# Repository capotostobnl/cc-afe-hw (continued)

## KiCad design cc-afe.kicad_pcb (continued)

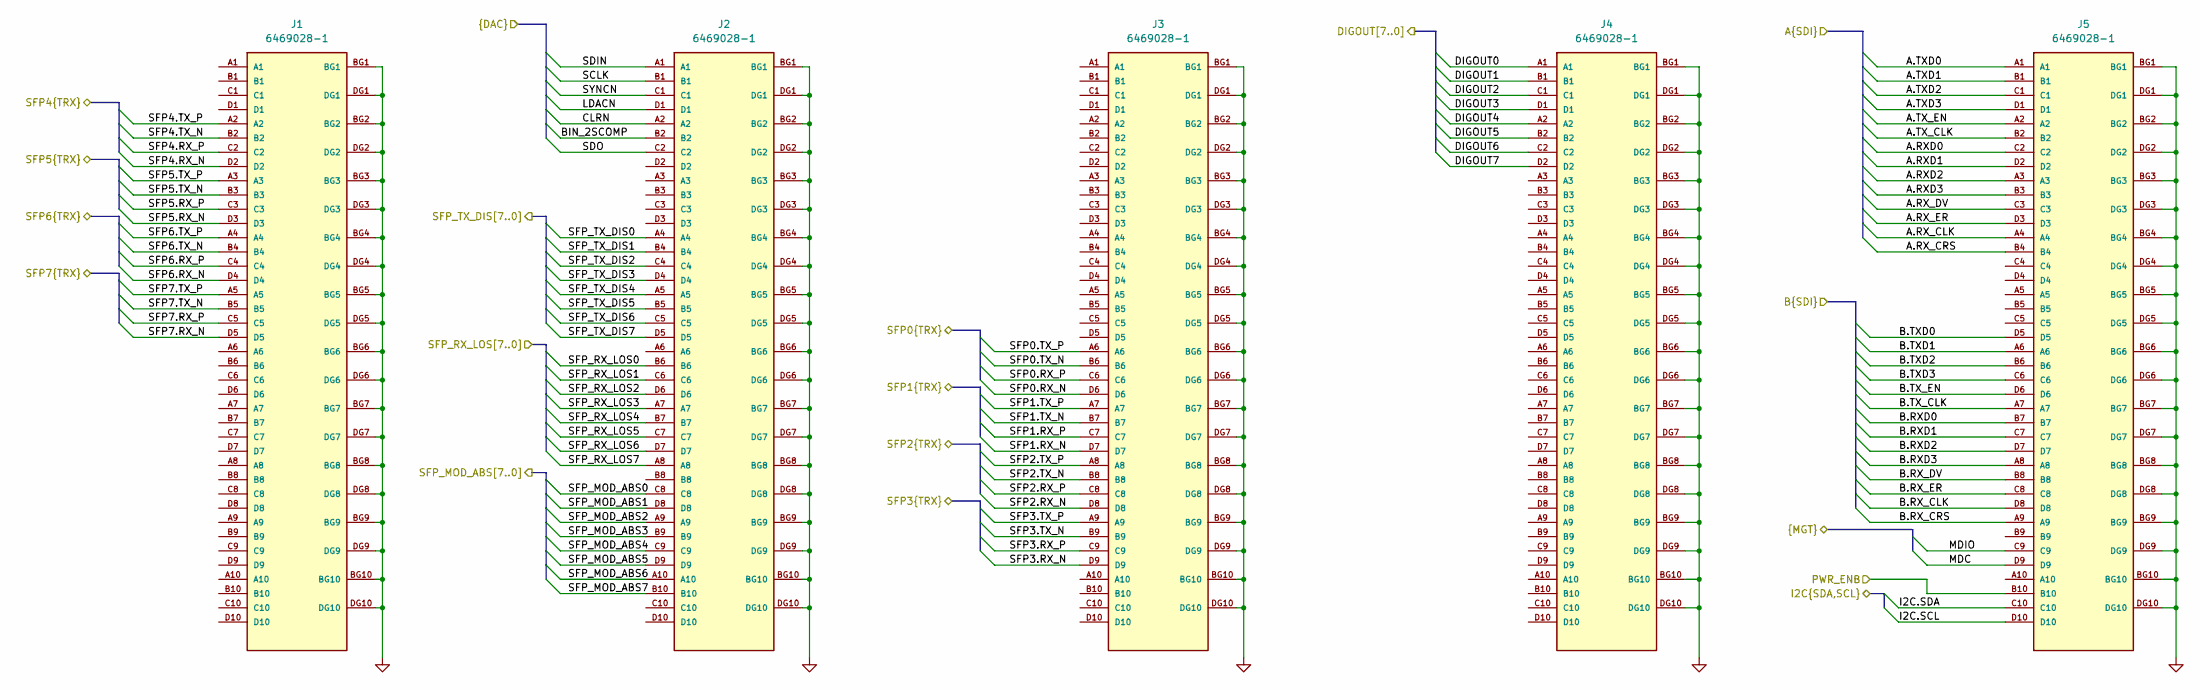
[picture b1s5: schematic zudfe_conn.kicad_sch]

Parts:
J1, J2, J3, J4, J5: 6469028-1; TE_6469028-1; PARTREV E

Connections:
/DAC/BIN_2SCOMP: J2.B2; also elsewhere on the board
/DAC/CLRN: J2.A2; also elsewhere on the board
/DAC/LDACN: J2.D1; also elsewhere on the board
/DAC/SCLK: J2.B1; also elsewhere on the board
/DAC/SDIN: J2.A1; also elsewhere on the board
/DAC/SDO: J2.C2
/DAC/SYNCN: J2.C1; also elsewhere on the board
/Digital Outputs/DIGOUT0: J4.A1; also elsewhere on the board
/Digital Outputs/DIGOUT1: J4.B1; also elsewhere on the board
/Digital Outputs/DIGOUT2: J4.C1; also elsewhere on the board
/Digital Outputs/DIGOUT3: J4.D1; also elsewhere on the board
/Digital Outputs/DIGOUT4: J4.A2; also elsewhere on the board
/Digital Outputs/DIGOUT5: J4.B2; also elsewhere on the board
/Digital Outputs/DIGOUT6: J4.C2; also elsewhere on the board
/Digital Outputs/DIGOUT7: J4.D2; also elsewhere on the board
/Regulators/PWR_ENB: J5.B10; also elsewhere on the board
/SDI/A.RXD0: J5.C2; also elsewhere on the board
/SDI/A.RXD1: J5.D2; also elsewhere on the board
/SDI/A.RXD2: J5.A3; also elsewhere on the board
/SDI/A.RXD3: J5.B3; also elsewhere on the board
/SDI/A.RX_CLK: J5.A4; also elsewhere on the board
/SDI/A.RX_CRS: J5.B4; also elsewhere on the board
/SDI/A.RX_DV: J5.C3; also elsewhere on the board
/SDI/A.RX_ER: J5.D3; also elsewhere on the board
/SDI/A.TXD0: J5.A1; also elsewhere on the board
/SDI/A.TXD1: J5.B1; also elsewhere on the board
/SDI/A.TXD2: J5.C1; also elsewhere on the board
/SDI/A.TXD3: J5.D1; also elsewhere on the board
/SDI/A.TX_CLK: J5.B2; also elsewhere on the board
/SDI/A.TX_EN: J5.A2; also elsewhere on the board
/SDI/B.RXD0: J5.B7; also elsewhere on the board
/SDI/B.RXD1: J5.C7; also elsewhere on the board
/SDI/B.RXD2: J5.D7; also elsewhere on the board
/SDI/B.RXD3: J5.A8; also elsewhere on the board
/SDI/B.RX_CLK: J5.D8; also elsewhere on the board
/SDI/B.RX_CRS: J5.A9; also elsewhere on the board
/SDI/B.RX_DV: J5.B8; also elsewhere on the board
/SDI/B.RX_ER: J5.C8; also elsewhere on the board
/SDI/B.TXD0: J5.D5; also elsewhere on the board
/SDI/B.TXD1: J5.A6; also elsewhere on the board
/SDI/B.TXD2: J5.B6; also elsewhere on the board
/SDI/B.TXD3: J5.C6; also elsewhere on the board
/SDI/B.TX_CLK: J5.A7; also elsewhere on the board
/SDI/B.TX_EN: J5.D6; also elsewhere on the board
/SDI/MDC: J5.D9; also elsewhere on the board
/SDI/MDIO: J5.C9; also elsewhere on the board
/SFP/I2C.SCL: J5.D10; also elsewhere on the board
/SFP/I2C.SDA: J5.C10; also elsewhere on the board
/SFP/SFP0.RX_N: J3.D6; also elsewhere on the board
/SFP/SFP0.RX_P: J3.C6; also elsewhere on the board
/SFP/SFP0.TX_N: J3.B6; also elsewhere on the board
/SFP/SFP0.TX_P: J3.A6; also elsewhere on the board
/SFP/SFP1.RX_N: J3.D7; also elsewhere on the board
/SFP/SFP1.RX_P: J3.C7; also elsewhere on the board
/SFP/SFP1.TX_N: J3.B7; also elsewhere on the board
/SFP/SFP1.TX_P: J3.A7; also elsewhere on the board
/SFP/SFP2.RX_N: J3.D8; also elsewhere on the board
/SFP/SFP2.RX_P: J3.C8; also elsewhere on the board
/SFP/SFP2.TX_N: J3.B8; also elsewhere on the board
/SFP/SFP2.TX_P: J3.A8; also elsewhere on the board
/SFP/SFP3.RX_N: J3.D9; also elsewhere on the board
/SFP/SFP3.RX_P: J3.C9; also elsewhere on the board
/SFP/SFP3.TX_N: J3.B9; also elsewhere on the board
/SFP/SFP3.TX_P: J3.A9; also elsewhere on the board
/SFP/SFP4.RX_N: J1.D2; also elsewhere on the board
/SFP/SFP4.RX_P: J1.C2; also elsewhere on the board
/SFP/SFP4.TX_N: J1.B2; also elsewhere on the board
/SFP/SFP4.TX_P: J1.A2; also elsewhere on the board
/SFP/SFP5.RX_N: J1.D3; also elsewhere on the board
/SFP/SFP5.RX_P: J1.C3; also elsewhere on the board
/SFP/SFP5.TX_N: J1.B3; also elsewhere on the board
/SFP/SFP5.TX_P: J1.A3; also elsewhere on the board
/SFP/SFP6.RX_N: J1.D4; also elsewhere on the board
/SFP/SFP6.RX_P: J1.C4; also elsewhere on the board
/SFP/SFP6.TX_N: J1.B4; also elsewhere on the board
/SFP/SFP6.TX_P: J1.A4; also elsewhere on the board
/SFP/SFP7.RX_N: J1.D5; also elsewhere on the board
/SFP/SFP7.RX_P: J1.C5; also elsewhere on the board
/SFP/SFP7.TX_N: J1.B5; also elsewhere on the board
/SFP/SFP7.TX_P: J1.A5; also elsewhere on the board
/SFP/SFP_MOD_ABS0: J2.C8; also elsewhere on the board
/SFP/SFP_MOD_ABS1: J2.D8; also elsewhere on the board
/SFP/SFP_MOD_ABS2: J2.A9; also elsewhere on the board
/SFP/SFP_MOD_ABS3: J2.B9; also elsewhere on the board
/SFP/SFP_MOD_ABS4: J2.C9; also elsewhere on the board
/SFP/SFP_MOD_ABS5: J2.D9; also elsewhere on the board
/SFP/SFP_MOD_ABS6: J2.A10; also elsewhere on the board
/SFP/SFP_MOD_ABS7: J2.B10; also elsewhere on the board
/SFP/SFP_RX_LOS0: J2.B6; also elsewhere on the board
/SFP/SFP_RX_LOS1: J2.C6; also elsewhere on the board
/SFP/SFP_RX_LOS2: J2.D6; also elsewhere on the board
/SFP/SFP_RX_LOS3: J2.A7; also elsewhere on the board
/SFP/SFP_RX_LOS4: J2.B7; also elsewhere on the board
/SFP/SFP_RX_LOS5: J2.C7; also elsewhere on the board
/SFP/SFP_RX_LOS6: J2.D7; also elsewhere on the board
/SFP/SFP_RX_LOS7: J2.A8; also elsewhere on the board
/SFP/SFP_TX_DIS0: J2.A4; also elsewhere on the board
/SFP/SFP_TX_DIS1: J2.B4; also elsewhere on the board
/SFP/SFP_TX_DIS2: J2.C4; also elsewhere on the board
/SFP/SFP_TX_DIS3: J2.D4; also elsewhere on the board
/SFP/SFP_TX_DIS4: J2.A5; also elsewhere on the board
/SFP/SFP_TX_DIS5: J2.B5; also elsewhere on the board
/SFP/SFP_TX_DIS6: J2.C5; also elsewhere on the board
/SFP/SFP_TX_DIS7: J2.D5; also elsewhere on the board
GND: J1.BG1, J1.BG2, J1.BG3, J1.BG4, J1.BG5, J1.BG6, J1.BG7, J1.BG8, J1.BG9, J1.BG10, J1.DG1, J1.DG2, J1.DG3, J1.DG4, J1.DG5, J1.DG6, J1.DG7, J1.DG8, J1.DG9, J1.DG10, J2.BG1, J2.BG2, J2.BG3, J2.BG4, J2.BG5, J2.BG6, J2.BG7, J2.BG8, J2.BG9, J2.BG10, J2.DG1, J2.DG2, J2.DG3, J2.DG4, J2.DG5, J2.DG6, J2.DG7, J2.DG8, J2.DG9, J2.DG10, J3.BG1, J3.BG2, J3.BG3, J3.BG4, J3.BG5, J3.BG6, J3.BG7, J3.BG8, J3.BG9, J3.BG10, J3.DG1, J3.DG2, J3.DG3, J3.DG4, J3.DG5, J3.DG6, J3.DG7, J3.DG8, J3.DG9, J3.DG10, J4.BG1, J4.BG2, J4.BG3, J4.BG4, J4.BG5, J4.BG6, J4.BG7, J4.BG8, J4.BG9, J4.BG10, J4.DG1, J4.DG2, J4.DG3, J4.DG4, J4.DG5, J4.DG6, J4.DG7, J4.DG8, J4.DG9, J4.DG10, J5.BG1, J5.BG2, J5.BG3, J5.BG4, J5.BG5, J5.BG6, J5.BG7, J5.BG8, J5.BG9, J5.BG10, J5.DG1, J5.DG2, J5.DG3, J5.DG4, J5.DG5, J5.DG6, J5.DG7, J5.DG8, J5.DG9, J5.DG10; also elsewhere on the board

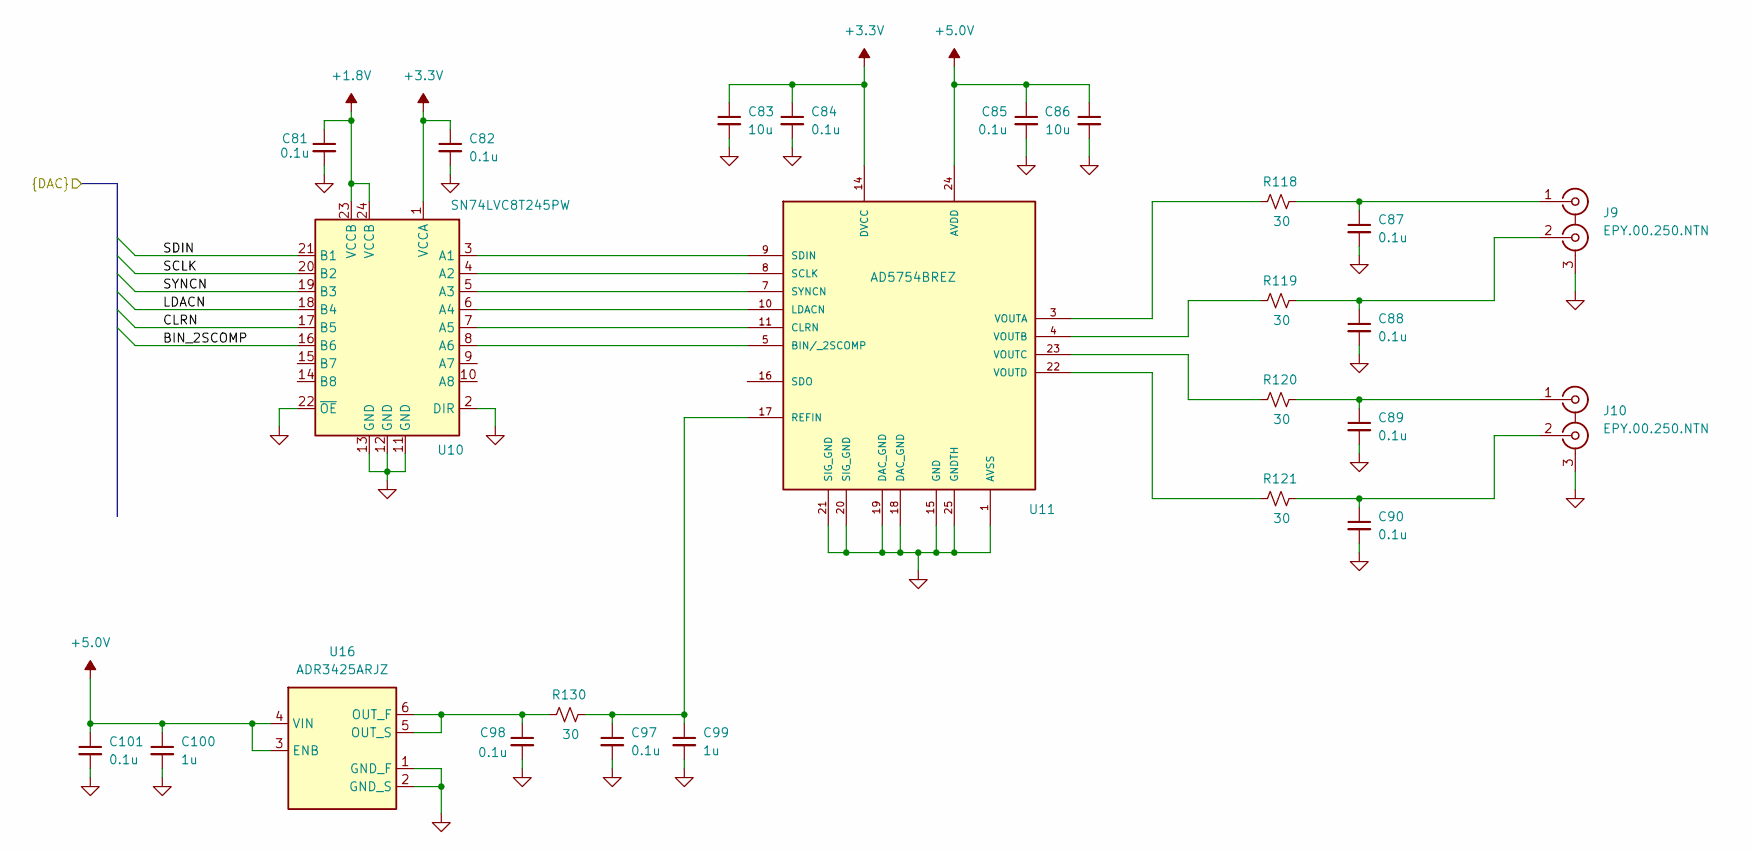
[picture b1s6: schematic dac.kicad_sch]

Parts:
C81, C82, C84, C85, C87, C88, C89, C90, C97, C98, C101: 0.1u; C_0603_1608Metric; Voltage 50; MFG_PN GCJ188R71H104KA12D
C83, C86: 10u; C_0805_2012Metric; MFG_PN GRM21BR61C106KE15K
C99, C100: 1u; C_0603_1608Metric; Voltage 50
J9, J10: EPY.00.250.NTN; LEMO_EPY.00.250.NTN; MFG_PN EPY.00.250.NTN
R118, R119, R120, R121, R130: 30; R_0603_1608Metric
U10: SN74LVC8T245PW; TSSOP-24_4.4x7.8mm_P0.65mm
U11: AD5754BREZ; SOP65P640X120-25N; MFG_PN AD5754BREZ
U16: ADR3425ARJZ; SOT95P280X145-6N; MFG_PN ADR3425ARJZ

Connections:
+1.8V: C81.1, U10.23 (VCCB), U10.24 (VCCB); also elsewhere on the board
+3.3V: C82.1, C83.1, C84.1, U10.1 (VCCA), U11.14 (DVCC); also elsewhere on the board
+5.0V: C85.1, C86.1, C100.1, C101.1, U11.24 (AVDD), U16.3 (ENB), U16.4 (VIN); also elsewhere on the board
/DAC/BIN_2SCOMP: U10.16 (B6); also elsewhere on the board
/DAC/CLRN: U10.17 (B5); also elsewhere on the board
/DAC/LDACN: U10.18 (B4); also elsewhere on the board
/DAC/SCLK: U10.20 (B2); also elsewhere on the board
/DAC/SDIN: U10.21 (B1); also elsewhere on the board
/DAC/SYNCN: U10.19 (B3); also elsewhere on the board
GND: C81.2, C82.2, C83.2, C84.2, C85.2, C86.2, C87.2, C88.2, C89.2, C90.2, C97.2, C98.2, C99.2, C100.2, C101.2, J9.3 (EXT), J10.3 (EXT), U10.2 (DIR), U10.11 (GND), U10.12 (GND), U10.13 (GND), U10.22 (~OE), U11.1 (AVSS), U11.15 (GND), U11.18 (DAC_GND), U11.19 (DAC_GND), U11.20 (SIG_GND), U11.21 (SIG_GND), U11.25 (GNDTH), U16.1 (GND_F), U16.2 (GND_S); also elsewhere on the board
unnamed: C87.1, J9.1 (IN1), R118.2
unnamed: C88.1, J9.2 (IN2), R119.2
unnamed: C89.1, J10.1 (IN1), R120.2
unnamed: C90.1, J10.2 (IN2), R121.2
unnamed: U10.3 (A1), U11.9 (SDIN)
unnamed: U10.4 (A2), U11.8 (SCLK)
unnamed: U10.5 (A3), U11.7 (SYNCN)
unnamed: U10.6 (A4), U11.10 (LDACN)
unnamed: U10.7 (A5), U11.11 (CLRN)
unnamed: U10.8 (A6), U11.5 (BIN/_2SCOMP)
unnamed: C97.1, C99.1, R130.2, U11.17 (REFIN)
unnamed: R118.1, U11.3 (VOUTA)
unnamed: R119.1, U11.4 (VOUTB)
unnamed: R120.1, U11.23 (VOUTC)
unnamed: R121.1, U11.22 (VOUTD)
unnamed: C98.1, R130.1, U16.5 (OUT_S), U16.6 (OUT_F)

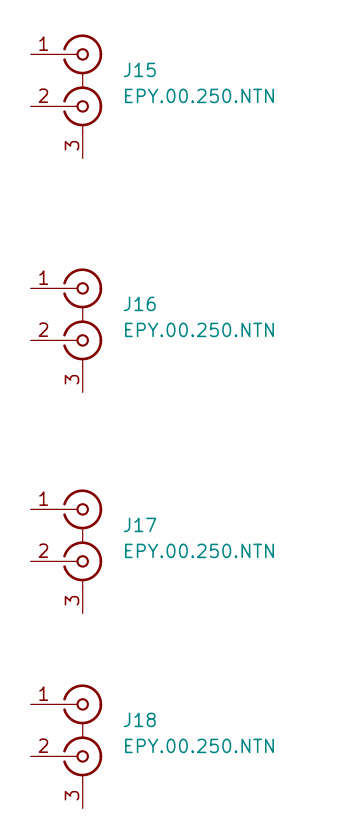
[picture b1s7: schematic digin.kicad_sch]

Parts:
J15, J16, J17, J18: EPY.00.250.NTN; LEMO_EPY.00.250.NTN; MFG_PN EPY.00.250.NTN

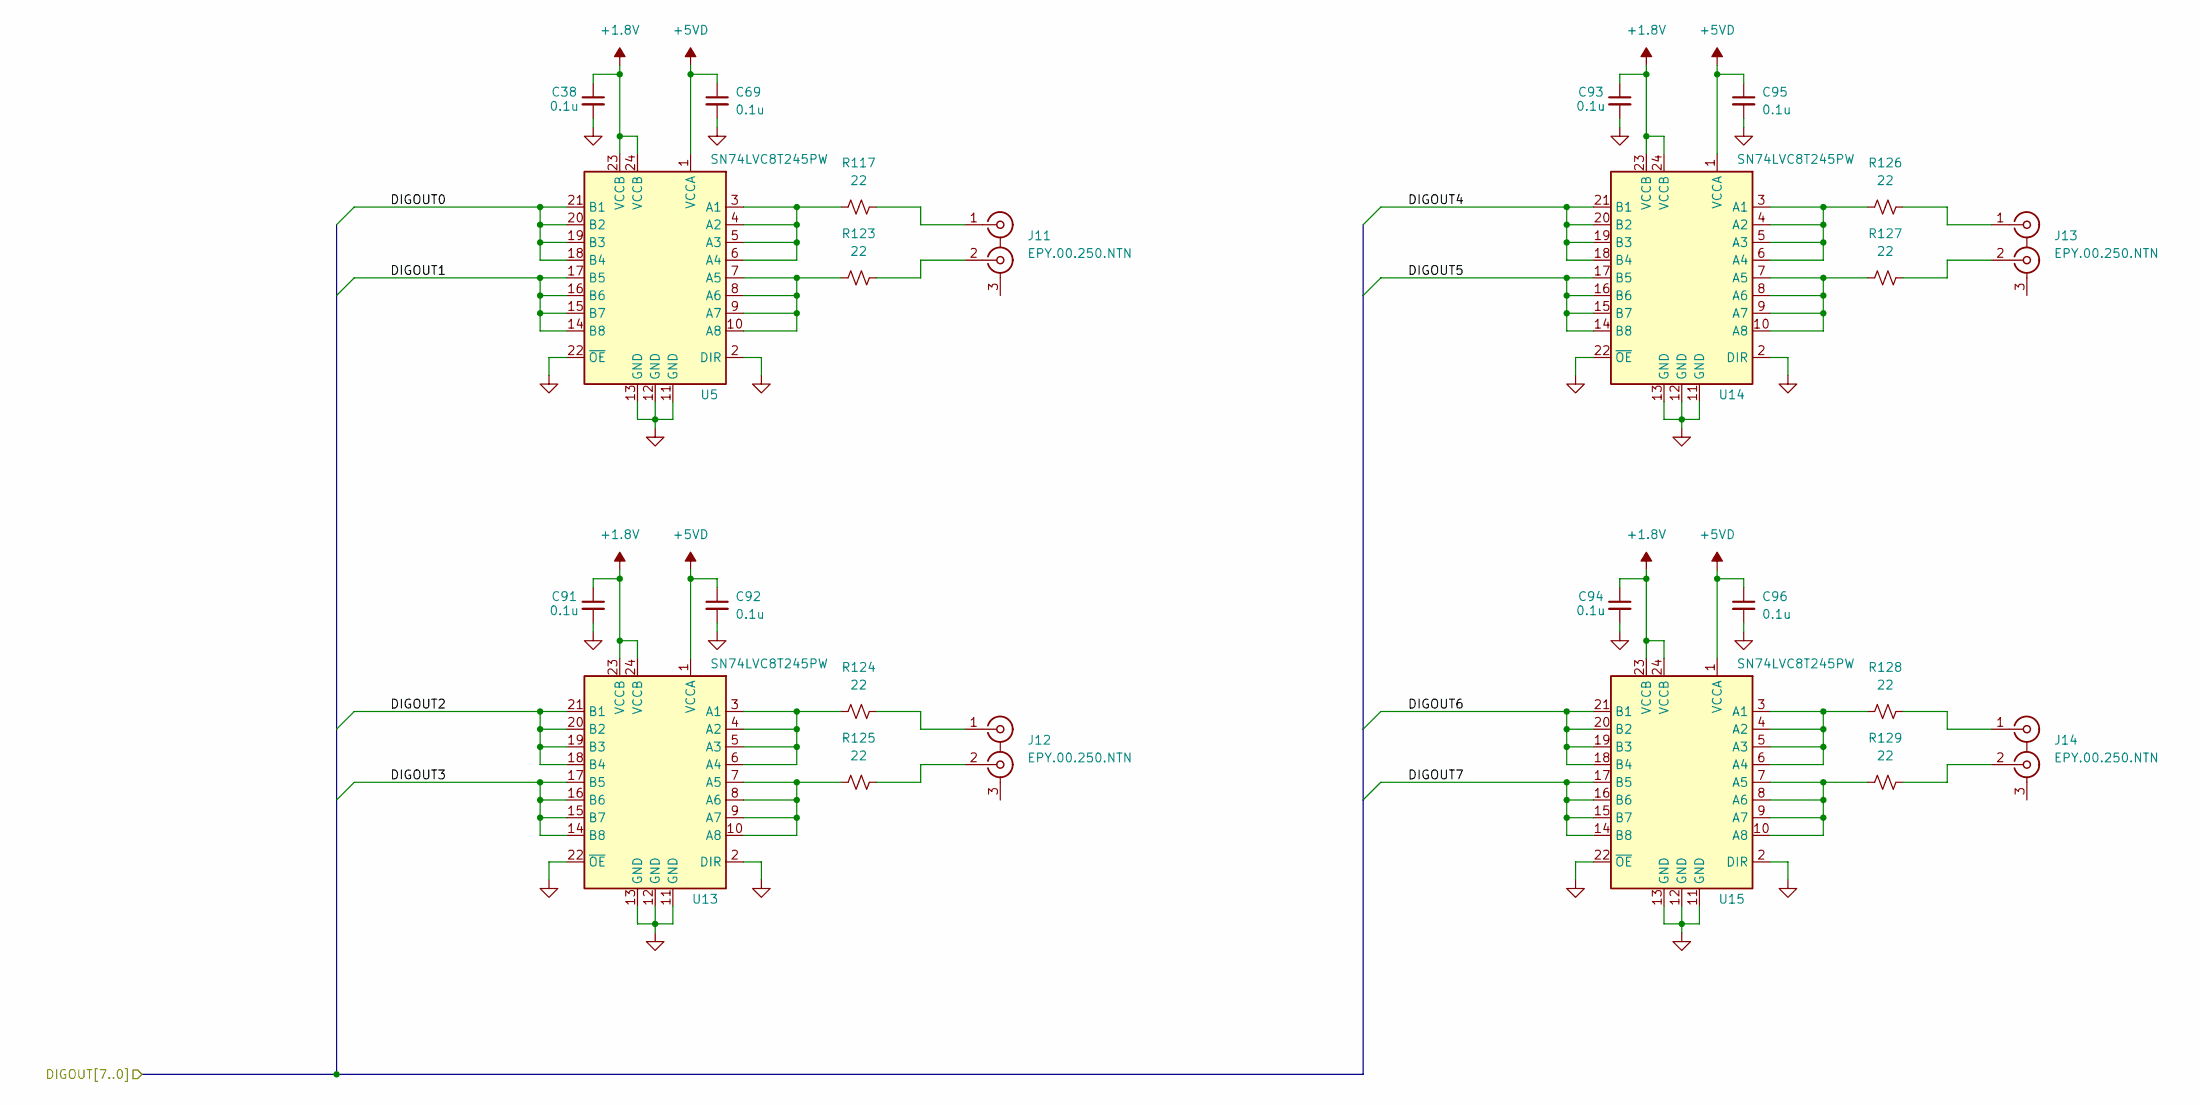
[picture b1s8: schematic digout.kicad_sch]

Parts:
C38, C69, C91, C92, C93, C94, C95, C96: 0.1u; C_0603_1608Metric; Voltage 50; MFG_PN GCJ188R71H104KA12D
J11, J12, J13, J14: EPY.00.250.NTN; LEMO_EPY.00.250.NTN; MFG_PN EPY.00.250.NTN
R117, R123, R124, R125, R126, R127, R128, R129: 22; R_1206_3216Metric; MFG_PN ERJ-3EKF49R9V
U5, U13, U14, U15: SN74LVC8T245PW; TSSOP-24_4.4x7.8mm_P0.65mm

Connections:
+1.8V: C38.1, C91.1, C93.1, C94.1, U5.23 (VCCB), U5.24 (VCCB), U13.23 (VCCB), U13.24 (VCCB), U14.23 (VCCB), U14.24 (VCCB), U15.23 (VCCB), U15.24 (VCCB); also elsewhere on the board
+5VD: C69.1, C92.1, C95.1, C96.1, U5.1 (VCCA), U13.1 (VCCA), U14.1 (VCCA), U15.1 (VCCA)
/Digital Outputs/DIGOUT0: U5.18 (B4), U5.19 (B3), U5.20 (B2), U5.21 (B1); also elsewhere on the board
/Digital Outputs/DIGOUT1: U5.14 (B8), U5.15 (B7), U5.16 (B6), U5.17 (B5); also elsewhere on the board
/Digital Outputs/DIGOUT2: U13.18 (B4), U13.19 (B3), U13.20 (B2), U13.21 (B1); also elsewhere on the board
/Digital Outputs/DIGOUT3: U13.14 (B8), U13.15 (B7), U13.16 (B6), U13.17 (B5); also elsewhere on the board
/Digital Outputs/DIGOUT4: U14.18 (B4), U14.19 (B3), U14.20 (B2), U14.21 (B1); also elsewhere on the board
/Digital Outputs/DIGOUT5: U14.14 (B8), U14.15 (B7), U14.16 (B6), U14.17 (B5); also elsewhere on the board
/Digital Outputs/DIGOUT6: U15.18 (B4), U15.19 (B3), U15.20 (B2), U15.21 (B1); also elsewhere on the board
/Digital Outputs/DIGOUT7: U15.14 (B8), U15.15 (B7), U15.16 (B6), U15.17 (B5); also elsewhere on the board
GND: C38.2, C69.2, C91.2, C92.2, C93.2, C94.2, C95.2, C96.2, U5.2 (DIR), U5.11 (GND), U5.12 (GND), U5.13 (GND), U5.22 (~OE), U13.2 (DIR), U13.11 (GND), U13.12 (GND), U13.13 (GND), U13.22 (~OE), U14.2 (DIR), U14.11 (GND), U14.12 (GND), U14.13 (GND), U14.22 (~OE), U15.2 (DIR), U15.11 (GND), U15.12 (GND), U15.13 (GND), U15.22 (~OE); also elsewhere on the board
unnamed: J11.1 (IN1), R117.2
unnamed: J11.2 (IN2), R123.2
unnamed: J12.1 (IN1), R124.2
unnamed: J12.2 (IN2), R125.2
unnamed: J13.1 (IN1), R126.2
unnamed: J13.2 (IN2), R127.2
unnamed: J14.1 (IN1), R128.2
unnamed: J14.2 (IN2), R129.2
unnamed: R117.1, U5.3 (A1), U5.4 (A2), U5.5 (A3), U5.6 (A4)
unnamed: R123.1, U5.7 (A5), U5.8 (A6), U5.9 (A7), U5.10 (A8)
unnamed: R124.1, U13.3 (A1), U13.4 (A2), U13.5 (A3), U13.6 (A4)
unnamed: R125.1, U13.7 (A5), U13.8 (A6), U13.9 (A7), U13.10 (A8)
unnamed: R126.1, U14.3 (A1), U14.4 (A2), U14.5 (A3), U14.6 (A4)
unnamed: R127.1, U14.7 (A5), U14.8 (A6), U14.9 (A7), U14.10 (A8)
unnamed: R128.1, U15.3 (A1), U15.4 (A2), U15.5 (A3), U15.6 (A4)
unnamed: R129.1, U15.7 (A5), U15.8 (A6), U15.9 (A7), U15.10 (A8)

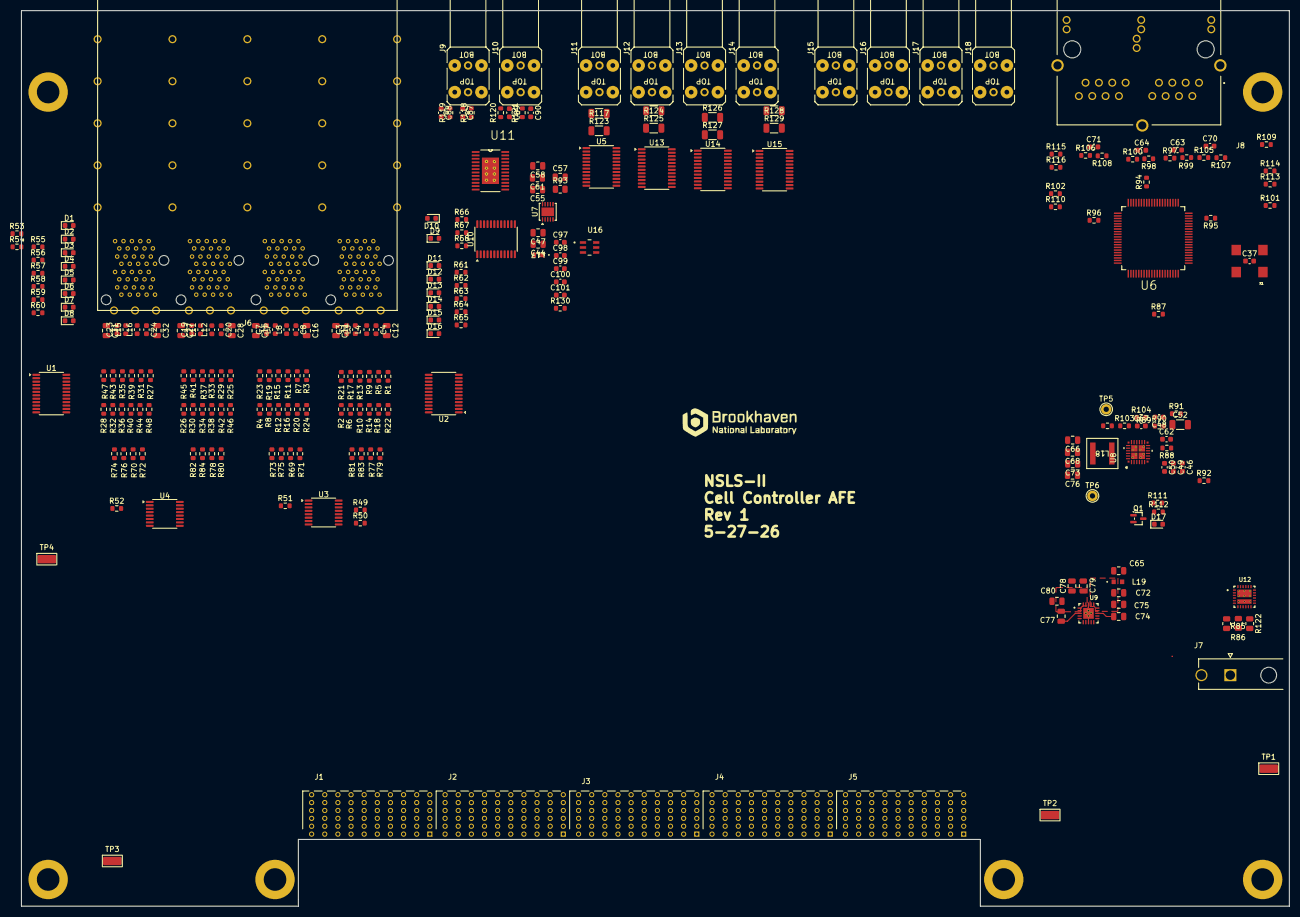
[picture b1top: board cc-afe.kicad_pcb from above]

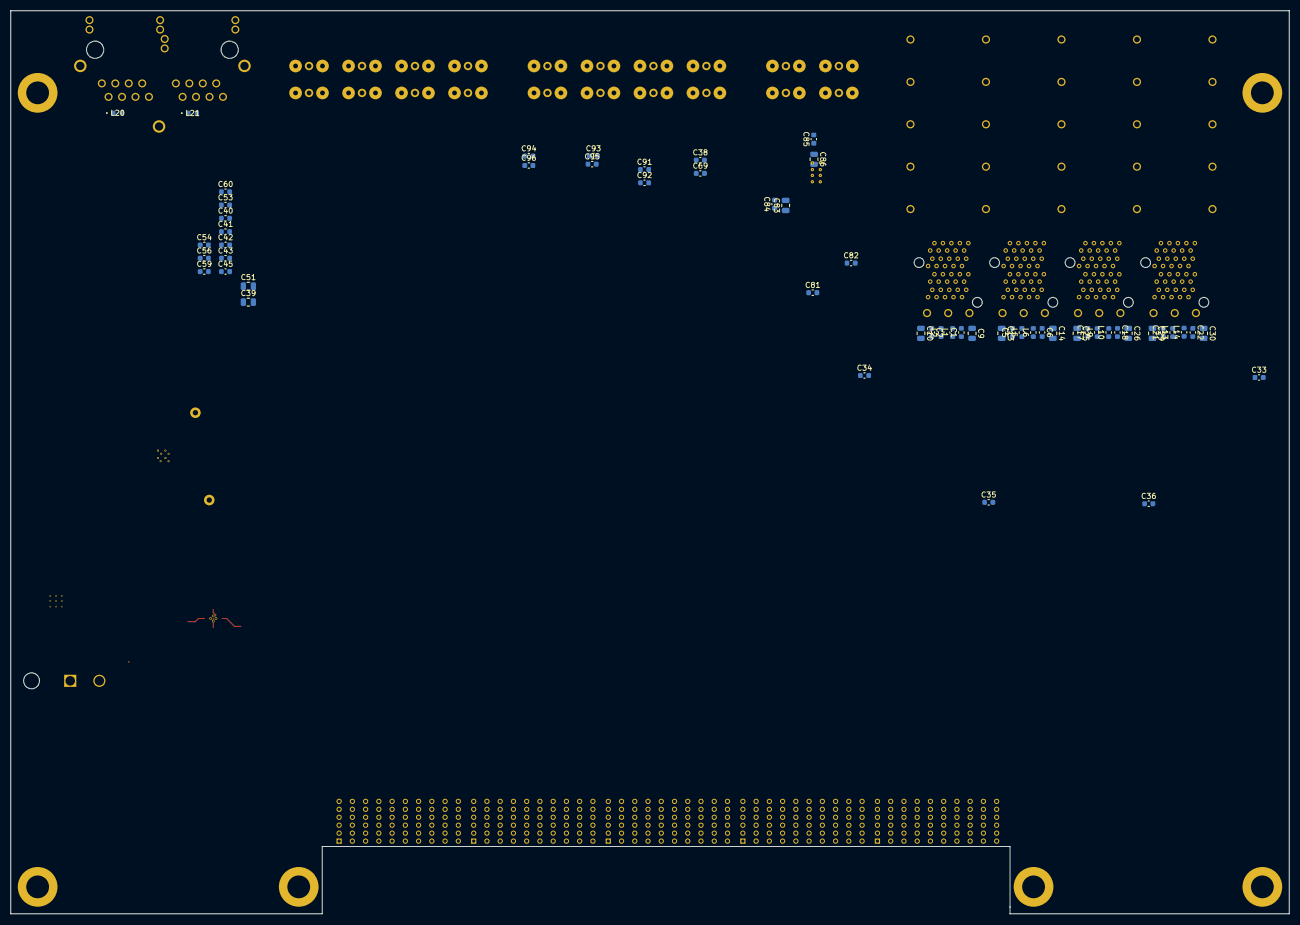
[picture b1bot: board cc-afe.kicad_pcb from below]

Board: 6 copper layers, 241.3 x 170.4 mm, 317 parts (56 on the bottom side), 280 nets.

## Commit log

2026-06-03 Finish Regulator section
2026-06-04 Place SFP passives
2026-06-04 Remove more unused schematics
2026-06-05 Add digital Outputs
